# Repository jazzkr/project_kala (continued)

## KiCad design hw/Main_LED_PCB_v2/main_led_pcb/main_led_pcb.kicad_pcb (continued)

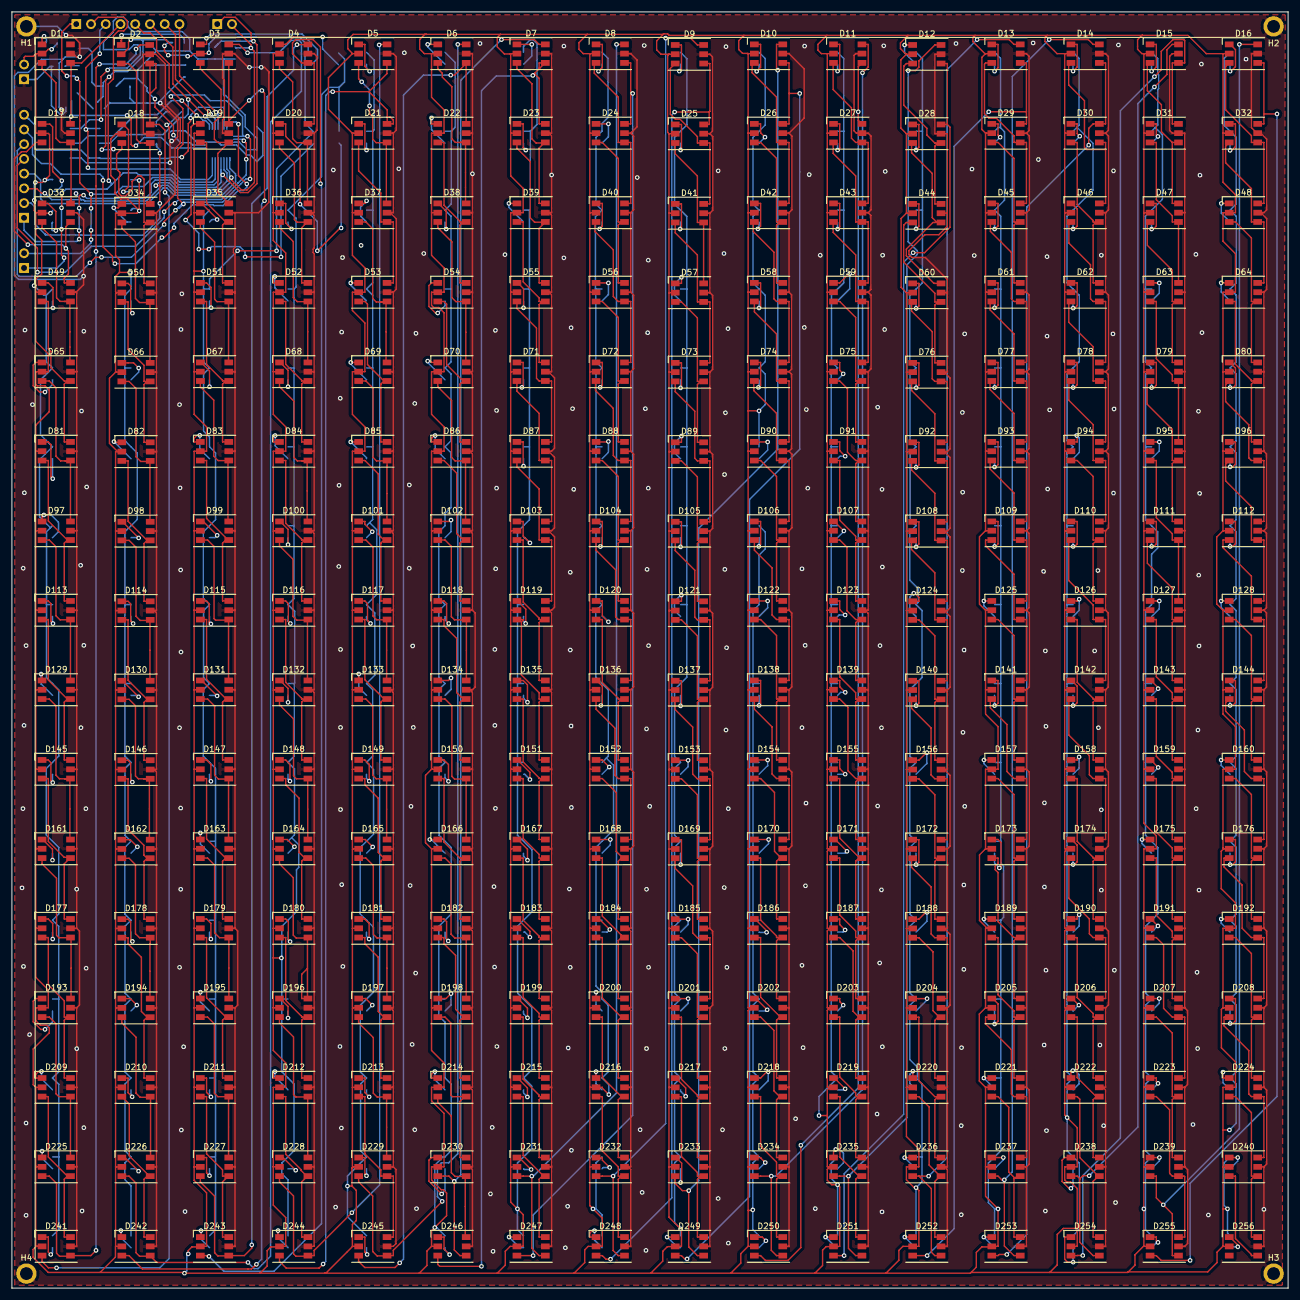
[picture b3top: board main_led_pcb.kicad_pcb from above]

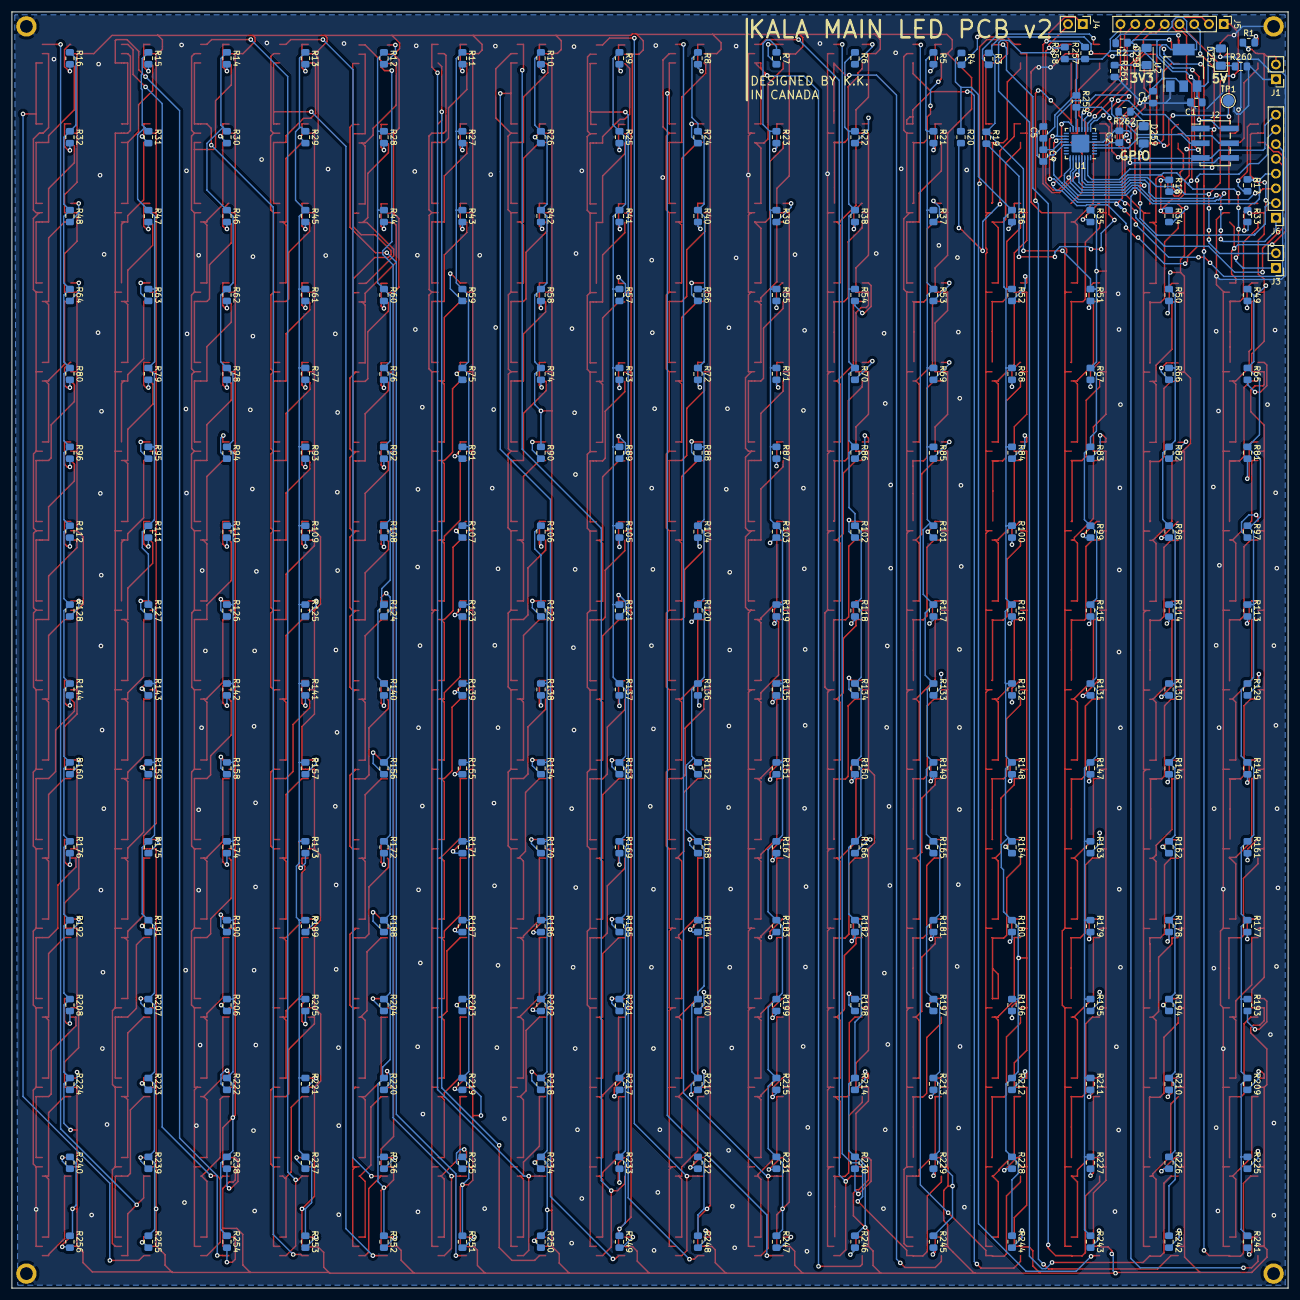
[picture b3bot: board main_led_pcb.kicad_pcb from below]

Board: 2 copper layers, 220.0 x 220.0 mm, 539 parts (279 on the bottom side), 533 nets.

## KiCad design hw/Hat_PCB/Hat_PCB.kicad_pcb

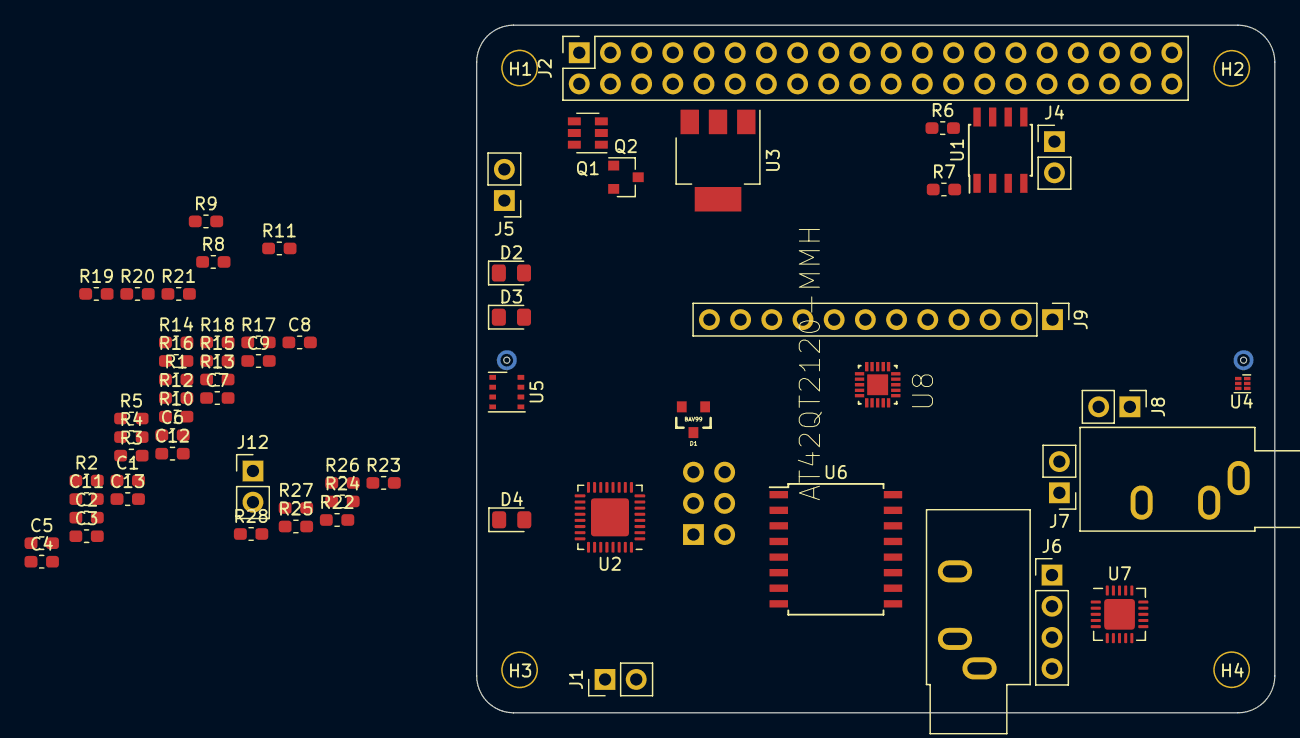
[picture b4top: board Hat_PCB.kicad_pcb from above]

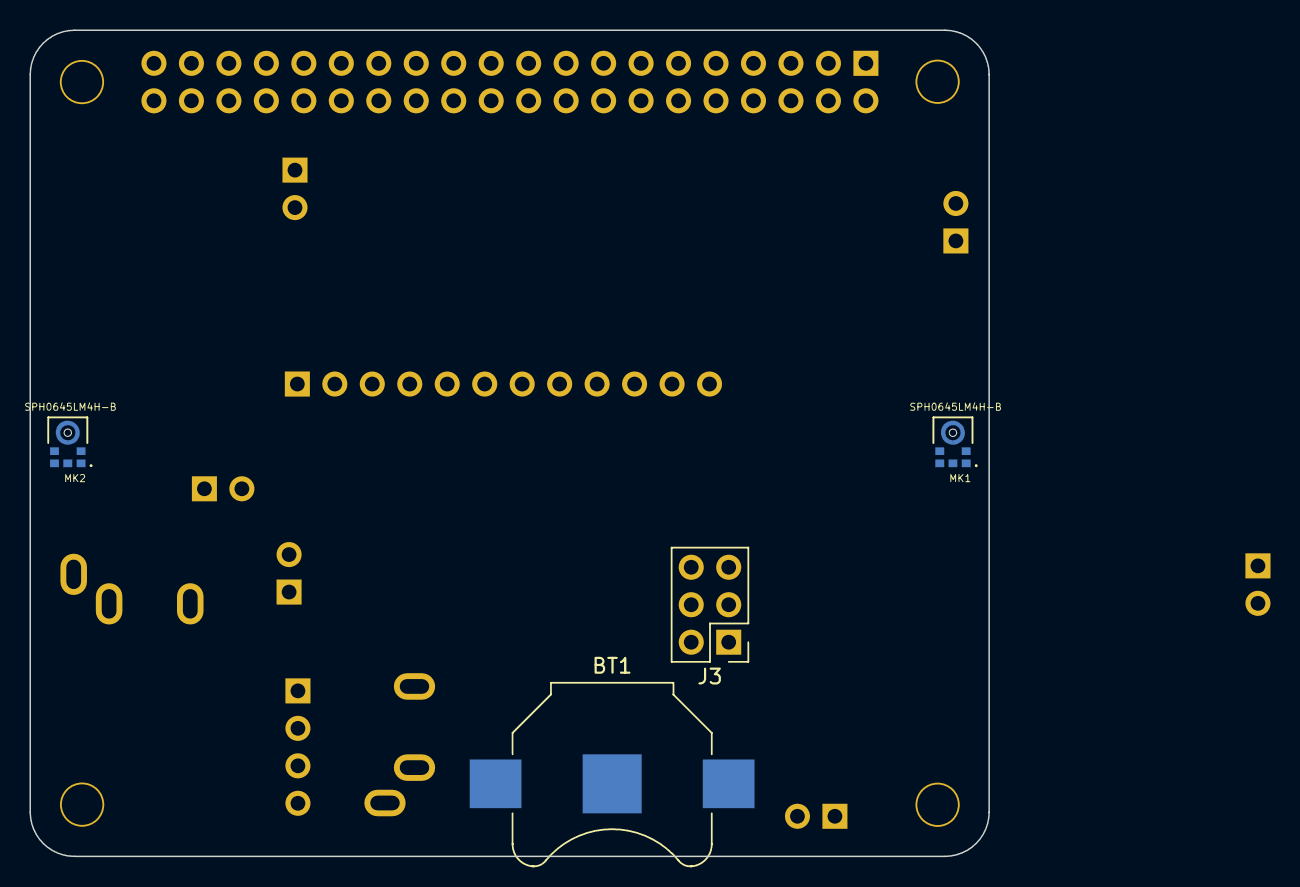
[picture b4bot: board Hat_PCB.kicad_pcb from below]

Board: 2 copper layers, 65.0 x 56.0 mm, 73 parts (4 on the bottom side), 61 nets, no tracks yet.

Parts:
BT1: Battery_Cell; BatteryHolder_Keystone_3000_1x12mm
C1, C4, C5, C12, C13: 10uF; C_0603_1608Metric_Pad1.05x0.95mm_HandSolder
C2, C3, C6, C7, C8, C9, C11: 0.1uF; C_0603_1608Metric_Pad1.05x0.95mm_HandSolder
D1: BAV99; SOT23-3
D2: 5V_LED; D_0805_2012Metric_Pad1.15x1.40mm_HandSolder
D3: 3V3_LED; D_0805_2012Metric_Pad1.15x1.40mm_HandSolder
D4: GPIO_LED; D_0805_2012Metric_Pad1.15x1.40mm_HandSolder
H1, H2, H3, H4: 3mm_Mounting_Hole; NPTH_3mm_ID
J1: EE_WP; PinHeader_1x02_P2.54mm_Vertical
J2: 40HAT; PinSocket_2x20_P2.54mm_Vertical
J3: AVR-ISP-6; PinHeader_2x03_P2.54mm_Vertical
J4: ID_I2C; PinHeader_1x02_P2.54mm_Vertical
J5: RPi_Power; PinHeader_1x02_P2.54mm_Vertical
J6: AUD_IN; PinHeader_1x04_P2.54mm_Vertical
J7: OUT_SPK_L; PinHeader_1x02_P2.54mm_Vertical
J8: OUT_SPK_R; PinHeader_1x02_P2.54mm_Vertical
J9: CAP_TOUCH; PinHeader_1x12_P2.54mm_Vertical
J10: AudioJack3; Jack_3.5mm_CUI_SJ1-3533NG_Horizontal
J11: AudioJack3_Ground; Jack_3.5mm_CUI_SJ1-3533NG_Horizontal
J12: I2C; PinHeader_1x02_P2.54mm_Vertical
MK1, MK2: SPH0645LM4H-B; MIC_SPH0645LM4H-B
Q1: DMMT5401; SOT-23-6
Q2: DMG2305UX; SOT-23
R1, R2, R3, R8, R9, R24, R25: 33R; R_0603_1608Metric_Pad1.05x0.95mm_HandSolder
R4: DNP; R_0603_1608Metric_Pad1.05x0.95mm_HandSolder
R5, R20, R22: 330R; R_0603_1608Metric_Pad1.05x0.95mm_HandSolder
R6, R7, R26, R27: 3.9K; R_0603_1608Metric_Pad1.05x0.95mm_HandSolder
R10, R11, R13, R14, R15, R21, R23: 10K; R_0603_1608Metric_Pad1.05x0.95mm_HandSolder
R12, R28: 47K; R_0603_1608Metric_Pad1.05x0.95mm_HandSolder
R16: 68R; R_0603_1608Metric_Pad1.05x0.95mm_HandSolder
R17, R18, R19: 0R; R_0603_1608Metric_Pad1.05x0.95mm_HandSolder
U1: CAT24C32; SOIC-8_3.9x4.9mm_P1.27mm
U2: ATtiny87-MU; QFN-32-1EP_5x5mm_P0.5mm_EP3.1x3.1mm
U3: NCP1117-3.3_SOT223; SOT-223-3_TabPin2
U4: TSL2591; DFN-6_1.3x1.2mm_P0.4mm
U5: BME680; Bosch_LGA-8_3x3mm_P0.8mm_ClockwisePinNumbering
U6: DS3231M; SOIC-16W_7.5x10.3mm_P1.27mm
U7: TPA2016D2RTJR; QFN-20-1EP_4x4mm_P0.5mm_EP2.5x2.5mm
U8: AT42QT2120-MMH; QFN45P300X300X85-21N

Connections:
+3V3: C2.1, C3.1, C4.1, C5.1, C6.1, C7.1, C8.1, C9.1, C11.1, C12.1, C13.1, D1.2, D3.2, J3.2, MK1.5, MK2.5, R6.1, R7.1, R11.1, R13.1, R15.2, R17.1, R21.1, R23.2, R26.1, R27.1, R28.1, U1.8, U2.4, U2.20, U3.2, U4.5, U5.2, U5.5, U5.6, U5.8, U6.2, U7.4, U7.5, U7.11, U7.12, U7.13, U8.9
+5V: C1.1, D2.2, J2.2, J2.4, Q1.5, Q2.2, U3.3
/ALS_INT: R13.2, U4.2
/AUD_IN_L+: J6.4, J10.T, U7.1
/AUD_IN_L-: J6.3, R18.1, U7.2
/AUD_IN_R+: J6.1, J10.R, U7.15
/AUD_IN_R-: J6.2, R18.2, R19.1, U7.14
/AUD_O_L+: J7.1, J11.T, U7.6
/AUD_O_L-: J7.2, U7.7
/AUD_O_R+: J8.1, J11.R, U7.10
/AUD_O_R-: J8.2, U7.9
/AUD_SDN: R17.2, U7.18
/GPIO_PB1: D4.2, U2.27
/ID_SC: J2.28, J4.2, R7.2, U1.5
/ID_SD: J2.27, J4.1, R6.2, U1.6
/MCU_RXD: R24.2, U2.29
/MCU_TXD: R25.2, U2.30
/MIC_CLK: J2.12, MK1.4, MK2.4
/MIC_DO: J2.38, R16.2
/MIC_WS: J2.35, MK1.1, MK2.1
/PROG_MISO: J3.1, R2.1, U2.31
/PROG_MOSI: J3.4, R1.1, U2.9
/PROG_RST_N: D1.3, J3.5, R8.2, R11.2, U2.14
/PROG_SCK: J3.3, R3.1, U2.10
/PSUP_5V: J5.2, Q1.6, Q2.3
/Pi_3V3: J2.1, J2.17
/SCL: J2.5, J12.2, R27.2, U2.26, U4.1, U5.4, U6.16, U7.17, U8.11
/SDA: J2.3, J12.1, R26.2, U2.28, U4.6, U5.3, U6.15, U7.19, U8.14
/SPI_CS_N: R9.2, U2.11
GND: BT1.2, C1.2, C2.2, C3.2, C4.2, C5.2, C6.2, C7.2, C8.2, C9.2, C11.2, C12.2, C13.2, D1.1, J1.1, J2.6, J2.9, J2.14, J2.20, J2.25, J2.30, J2.34, J2.39, J3.6, J5.1, J10.S, J11.S, MK1.3, R4.2, R5.1, R10.2, R12.2, R14.2, R19.2, R20.1, R22.1, U1.1, U1.2, U1.3, U1.4, U2.5, U2.21, U2.33, U3.1, U4.3, U5.1, U5.7, U6.5, U6.6, U6.7, U6.8, U6.9, U6.10, U6.11, U6.12, U6.13, U7.3, U7.8, U7.21, U8.8, U8.10, U8.21
unnamed: BT1.1, U6.14
unnamed: D2.1, R5.2
unnamed: D3.1, R20.2
unnamed: D4.1, R22.2
unnamed: J1.2, R4.1, R23.1, U1.7
unnamed: J2.8, R24.1
unnamed: J2.10, R25.1
unnamed: J2.19, R1.2
unnamed: J2.21, R2.2
unnamed: J2.22, R8.1
unnamed: J2.23, R3.2
unnamed: J2.24, R9.1
unnamed: J9.1, U8.7
unnamed: J9.2, U8.6
unnamed: J9.3, U8.5
unnamed: J9.4, U8.4
unnamed: J9.5, U8.3
unnamed: J9.6, U8.2
unnamed: J9.7, U8.1
unnamed: J9.8, U8.20
unnamed: J9.9, U8.19
unnamed: J9.10, U8.18
unnamed: J9.11, U8.17
unnamed: J9.12, U8.16
unnamed: MK1.2, R14.1
unnamed: MK1.6, MK2.6, R16.1
unnamed: MK2.2, R15.1
unnamed: Q1.1, Q1.2, Q1.3, R10.1
unnamed: Q1.4, Q2.1, R12.1
unnamed: R21.2, U8.12
unnamed: R28.2, U8.15

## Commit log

2018-08-15 Committing progress up until now
2018-08-15 Final touches on LED pcb
2019-01-13 Re-org to use kicad for hat PCB
2019-01-13 Add schematic symbols for most components
2019-01-14 Schematic mostly done, started prelim layout
2019-01-17 Added RTC, changed layout a bit
2019-01-18 Added pull ups, LEDs, & swapped out cap touch IC
2019-01-23 change back RTC, finish placement mostly
2019-12-28 Commit WIP on new main LED PCB
2020-01-25 Add all files, sort out later
2020-02-06 Add gitignore for kicad, mac OS, python, C, C++:
2020-02-06 Add WiP pixel planner
2020-02-06 Fix grid system
2020-02-07 Add pixel color change capability
2020-02-07 Start to flesh out pixel frames & animations
2020-02-07 Small fix
2020-02-15 More work on pixel planner
2020-02-22 Save progress
2020-04-02 WiP, rearrange interface + add playback
2020-04-03 Changes to mechanical, PCBs, + pixel planner SW
2020-04-03 Update gitignore
2020-04-03 More gitignore tweaks
2020-04-05 Backlink to CADLAB.io has been added.
